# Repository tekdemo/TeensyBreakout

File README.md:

# Teensy Breakout

A small PCB to break out a Teensy into a form factor suitable for small electronics prototyping

# Features
- Adapts Teensy pinout to Arduino shield, so existing shields can be fit to a Teensy
- Adds LiPo battery monitoring and charging capability
- Adds three wire pinouts for all pins
- All PWM outputs have an LED
- All PWM outputs connect to 3 wire servo headers that supply input or battery voltage for use with servos or motor controllers
- Contains small Stormy logo on back since the [Stormbots](http://stormbots.com) were the inspiration for this board's existence

# BOM
Due to the nature of the breakout, many components can be omitted depending on the needed sections. 

## Components 
 Part | Quantity  | Description | Part Number
---|---|---|---
 Teensy | 1 | Teensy Microcontroller | [OSH Park][oshteensy] or [Adafruit][adateensy] or 
PCB | 1 | Bare PCB | [OSH Park][pcb]
LED |11| 0603 or 0805 LED | any
1uF cap  |2| 0603 or 0805 cap | any
0.1uF cap |4| 0603 or 0805 LED | any
10uF cap |2| 0603 or 0805 cap | any
LiPO Battery |4| Any with JST connector | [Adafruit][lipo]
JST Battery Connector |4|  | [JST-PH-2-THM-RA][JST-PH-2-THM-RA]
MCP73871| 2 | LiPO Battery Management IC | [MCP73871][MCP73871]
MCP1703| 2 | 3.3V voltage regulator | [MCP1703][MCP1703]
Large (100uF+ cap) |2| 0603 or larger | any

## Pin Connections
The various use cases may or may not require some or all of these pins. Here's the most you can solder to the board in the simplest orientation

Most of these can be swapped, omitted, or assembled with small 1x3 connectors or whatever you have on hand. Otherwise, they can be purchased at [Digikey](http://digikey.com) or [Adafruit](http://adafruit.com)

Part | Quantity  | Description 
---|---|---
Arduino Sockets | 2 | 0.1" 1x8 F socket 
Arduino Sockets | 2 | 0.1" 1x6 F socket 
3 wire output headers | 2 | 0.1" 3x8 M Angle Pins 
3 wire output headers | 1 | 0.1" 3x6 M Angle Pins 
Servo output headers | 2 | 0.1" 3x3 M 90 degree Pins 
Servo output headers | 1 | 0.1" 3x4 M 90 degree Pins 

[oshteensy]: http://store.oshpark.com/products/teensy-3-1
[adateensy]: https://www.adafruit.com/product/2756
[pcb]: https://oshpark.com/import?url=https://raw.githubusercontent.com/tekdemo/TeensyBreakout/master/TeensyBreakout.brd
[lipo]: https://www.adafruit.com/categories/574
[MCP1703]: http://www.digikey.com/product-detail/en/microchip-technology/MCP1703AT-3302E-CB/MCP1703AT-3302E-CBCT-ND/3598398
[MCP73871]: http://www.digikey.com/product-detail/en/microchip-technology/MCP73871-2CCI-ML/MCP73871-2CCI-ML-ND/1680971
[JST-PH-2-THM-RA]: http://www.digikey.com/product-detail/en/jst-sales-america-inc/S2B-PH-K-S(LF)(SN)/455-1719-ND/926626

# Special Thanks

Thanks to Adafruit, who supplied the base schematic for the Battery monitor IC. Awesome work.

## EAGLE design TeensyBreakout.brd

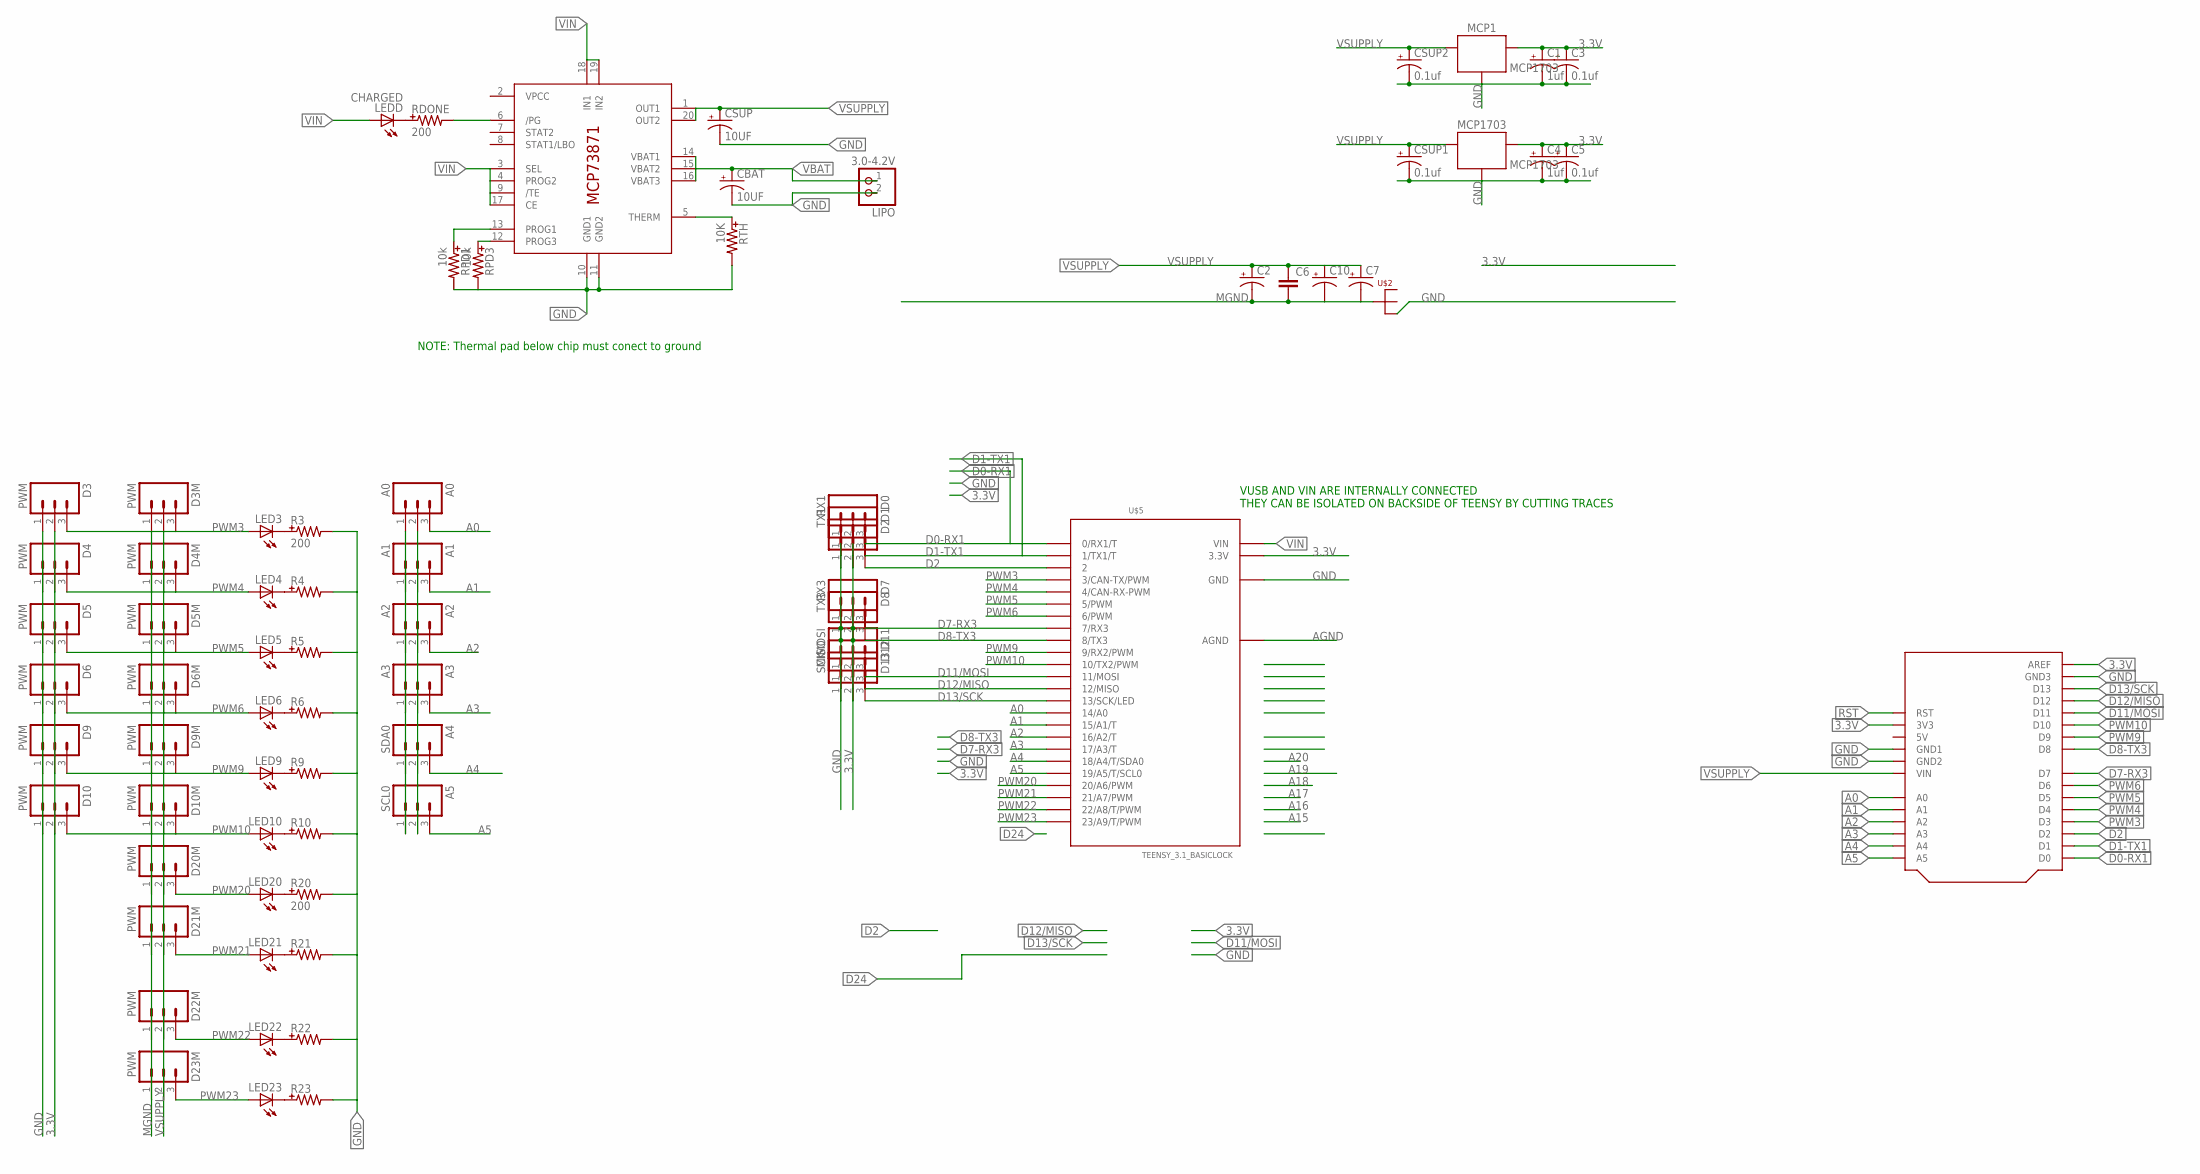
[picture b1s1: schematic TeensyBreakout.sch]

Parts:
A0: A0; 1X03_LOCK
A1: A1; 1X03_LOCK
A2: A2; 1X03_LOCK
A3: A3; 1X03_LOCK
A4: SDA0; 1X03_LOCK
A5: SCL0; 1X03_LOCK
C1, C4: 1uf; 0402-0603-0805-UNIVERSAL
C2, C7, C10: CAP-POLARIZEDUNIVERSAL; 0402-0603-0805-UNIVERSAL
C3, C5: 0.1uf; 0402-0603-0805-UNIVERSAL
C6: CAP1210; 1210
CBAT: 10UF; 0402-0603-0805-UNIVERSAL
CSUP: 10UF; 0402-0603-0805-UNIVERSAL
CSUP1, CSUP2: 0.1uf; 0402-0603-0805-UNIVERSAL
D0: RX1; 1X03_LOCK
D1: TX1; 1X03_LOCK
D2: M03LOCK; 1X03_LOCK
D3, D3M, D4, D4M, D5, D5M, D6, D6M, D9, D9M, D10, D10M, D20M, D21M, D22M, D23M: PWM; 1X03_LOCK
D7: RX3; 1X03_LOCK
D8: TX3; 1X03_LOCK
D11: MOSI; 1X03_LOCK
D12: MISO; 1X03_LOCK
D13: SCK; 1X03_LOCK
IC1: MCP73871; QFN20
LED3, LED4, LED5, LED6, LED9, LED10, LED20, LED21, LED22, LED23: LEDUNIVERSAL; 0402-0603-0805-UNIVERSAL
LEDD: CHARGED; 0402-0603-0805-UNIVERSAL
LIPO: 3.0-4.2V; JST-PH-2-THM-RA
MCP1, MCP1703: MCP1703; SOT23
R3, R20: 200; 0402-0603-0805-UNIVERSAL
R4, R5, R6, R9, R10, R21, R22, R23: RESISTORUNIVERSAL; 0402-0603-0805-UNIVERSAL
RDONE: 200; 0402-0603-0805-UNIVERSAL
RPD1, RPD3: 10k; 0402-0603-0805-UNIVERSAL
RTH: 10K; 0402-0603-0805-UNIVERSAL
U$2: NET-JUNCTION8-MIL-DIAMETER; NET-JUNCTION
U$4: ARDUINO
U$5: TEENSY_3.1_BASICLOCK; TEENSY_3.1_BASIC_LOCK

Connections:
3.3V: A0.2, A1.2, A2.2, A3.2, A4.2, A5.2, C1.+, C3.+, C4.+, C5.+, D0.2, D1.2, D2.2, D3.2, D4.2, D5.2, D6.2, D7.2, D8.2, D9.2, D10.2, D11.2, D12.2, D13.2, MCP1.2 (OUT), MCP1703.2 (OUT), U$4.3V3, U$4.AREF, U$5.3.3V
A0: A0.3, U$4.A0, U$5.14/A0
A1: A1.3, U$4.A1, U$5.15/A1 (15/A1/T)
A2: A2.3, U$4.A2, U$5.16/A2 (16/A2/T)
A3: A3.3, U$4.A3, U$5.17/A3 (17/A3/T)
A4: A4.3, U$4.A4, U$5.18/A4 (18/A4/T/SDA0)
A5: A5.3, U$4.A5, U$5.19/A5 (19/A5/T/SCL0)
AGND: U$5.AGND
D0-RX1: D0.3, U$4.D0, U$5.0 (0/RX1/T)
D1-TX1: D1.3, U$4.D1, U$5.1 (1/TX1/T)
D2: D2.3, U$4.D2, U$5.2
D7-RX3: D7.3, U$4.D7, U$5.7 (7/RX3)
D8-TX3: D8.3, U$4.D8, U$5.8 (8/TX3)
D11/MOSI: D11.3, U$4.D11, U$5.11 (11/MOSI)
D12/MISO: D12.3, U$4.D12, U$5.12 (12/MISO)
D13/SCK: D13.3, U$4.D13, U$5.13 (13/SCK/LED)
GND: A0.1, A1.1, A2.1, A3.1, A4.1, A5.1, C1.-, C3.-, C4.-, C5.-, CBAT.-, CSUP.-, CSUP1.-, CSUP2.-, D0.1, D1.1, D2.1, D3.1, D4.1, D5.1, D6.1, D7.1, D8.1, D9.1, D10.1, D11.1, D12.1, D13.1, IC1.10 (GND1), IC1.11 (GND2), LIPO.2 (1), MCP1.1 (GND), MCP1703.1 (GND), R3.- (2), R4.- (2), R5.- (2), R6.- (2), R9.- (2), R10.- (2), R20.- (2), R21.- (2), R22.- (2), R23.- (2), RPD1.- (2), RPD3.- (2), RTH.- (2), U$2.P$4 (3), U$4.GND1, U$4.GND2, U$4.GND3, U$5.GND
MGND: C2.-, C6.2, C7.-, C10.-, D3M.1, D4M.1, D5M.1, D6M.1, D9M.1, D10M.1, D20M.1, D21M.1, D22M.1, D23M.1, U$2.P$1 (1)
unnamed: IC1.5 (THERM), RTH.+ (1)
unnamed: IC1.12 (PROG3), RPD3.+ (1)
unnamed: IC1.13 (PROG1), RPD1.+ (1)
unnamed: IC1.6 (/PG), RDONE.- (2)
unnamed: LEDD.- (C), RDONE.+ (1)
unnamed: LED3.- (C), R3.+ (1)
unnamed: LED4.- (C), R4.+ (1)
unnamed: LED5.- (C), R5.+ (1)
unnamed: LED6.- (C), R6.+ (1)
unnamed: LED9.- (C), R9.+ (1)
unnamed: LED10.- (C), R10.+ (1)
unnamed: LED20.- (C), R20.+ (1)
unnamed: LED21.- (C), R21.+ (1)
unnamed: LED22.- (C), R22.+ (1)
unnamed: LED23.- (C), R23.+ (1)
PWM3: D3.3, D3M.3, LED3.+ (A), U$4.D3, U$5.3 (3/CAN-TX/PWM)
PWM4: D4.3, D4M.3, LED4.+ (A), U$4.D4, U$5.4 (4/CAN-RX-PWM)
PWM5: D5.3, D5M.3, LED5.+ (A), U$4.D5, U$5.5 (5/PWM)
PWM6: D6.3, D6M.3, LED6.+ (A), U$4.D6, U$5.6 (6/PWM)
PWM9: D9.3, D9M.3, LED9.+ (A), U$4.D9, U$5.9 (9/RX2/PWM)
PWM10: D10.3, D10M.3, LED10.+ (A), U$4.D10, U$5.10 (10/TX2/PWM)
PWM20: D20M.3, LED20.+ (A), U$5.20/A6 (20/A6/PWM)
PWM21: D21M.3, LED21.+ (A), U$5.21/A7 (21/A7/PWM)
PWM22: D22M.3, LED22.+ (A), U$5.22/A8 (22/A8/T/PWM)
PWM23: D23M.3, LED23.+ (A), U$5.23/A9 (23/A9/T/PWM)
RST: U$4.RST
VBAT: CBAT.+, IC1.14 (VBAT1), IC1.15 (VBAT2), IC1.16 (VBAT3), LIPO.1 (2)
VIN: IC1.3 (SEL), IC1.4 (PROG2), IC1.9 (/TE), IC1.17 (CE), IC1.18 (IN1), IC1.19 (IN2), LEDD.+ (A), U$5.VIN
VSUPPLY: C2.+, C6.1, C7.+, C10.+, CSUP.+, CSUP1.+, CSUP2.+, D3M.2, D4M.2, D5M.2, D6M.2, D9M.2, D10M.2, D20M.2, D21M.2, D22M.2, D23M.2, IC1.1 (OUT1), IC1.20 (OUT2), MCP1.3 (IN), MCP1703.3 (IN), U$4.VIN

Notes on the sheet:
VUSB AND VIN ARE INTERNALLY CONNECTED THEY CAN BE ISOLATED ON BACKSIDE OF TEENSY BY CUTTING TRACES
NOTE: Thermal pad below chip must conect to ground

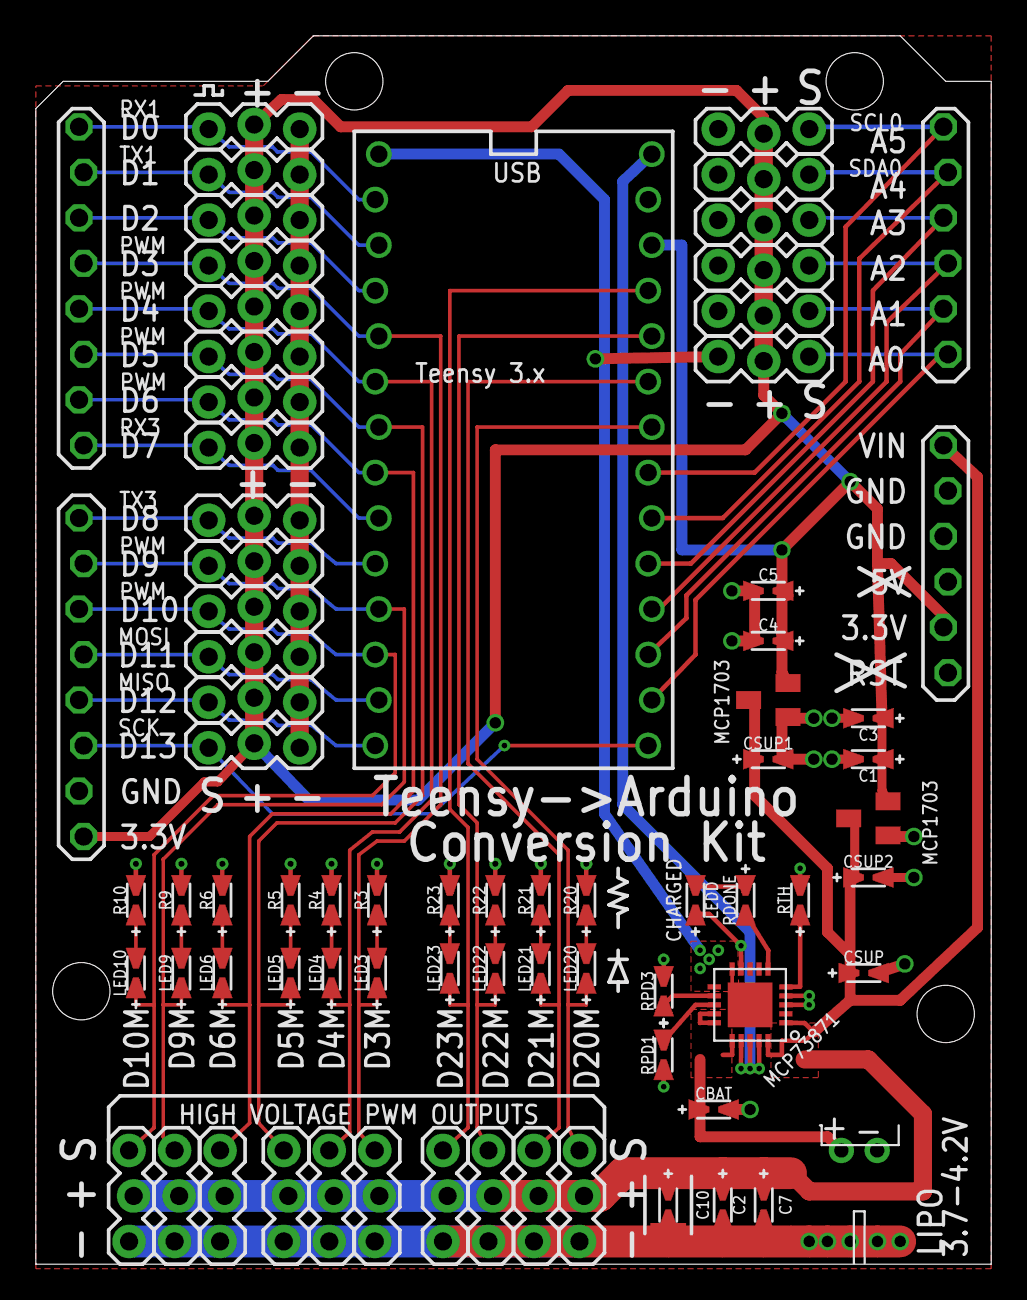
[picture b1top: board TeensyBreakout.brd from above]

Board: 2 copper layers, 53.3 x 68.6 mm, 74 parts (0 on the bottom side), 45 nets.

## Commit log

2015-11-04 Update locking headers, fix 2 missing wires
2016-06-19 Improve documentation
2016-06-19 Add BOM
2016-06-19 Forgot pictures
